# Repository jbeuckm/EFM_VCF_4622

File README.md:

# EFM_VCF_4622
Moog Taurus type Transistor Ladder LPF

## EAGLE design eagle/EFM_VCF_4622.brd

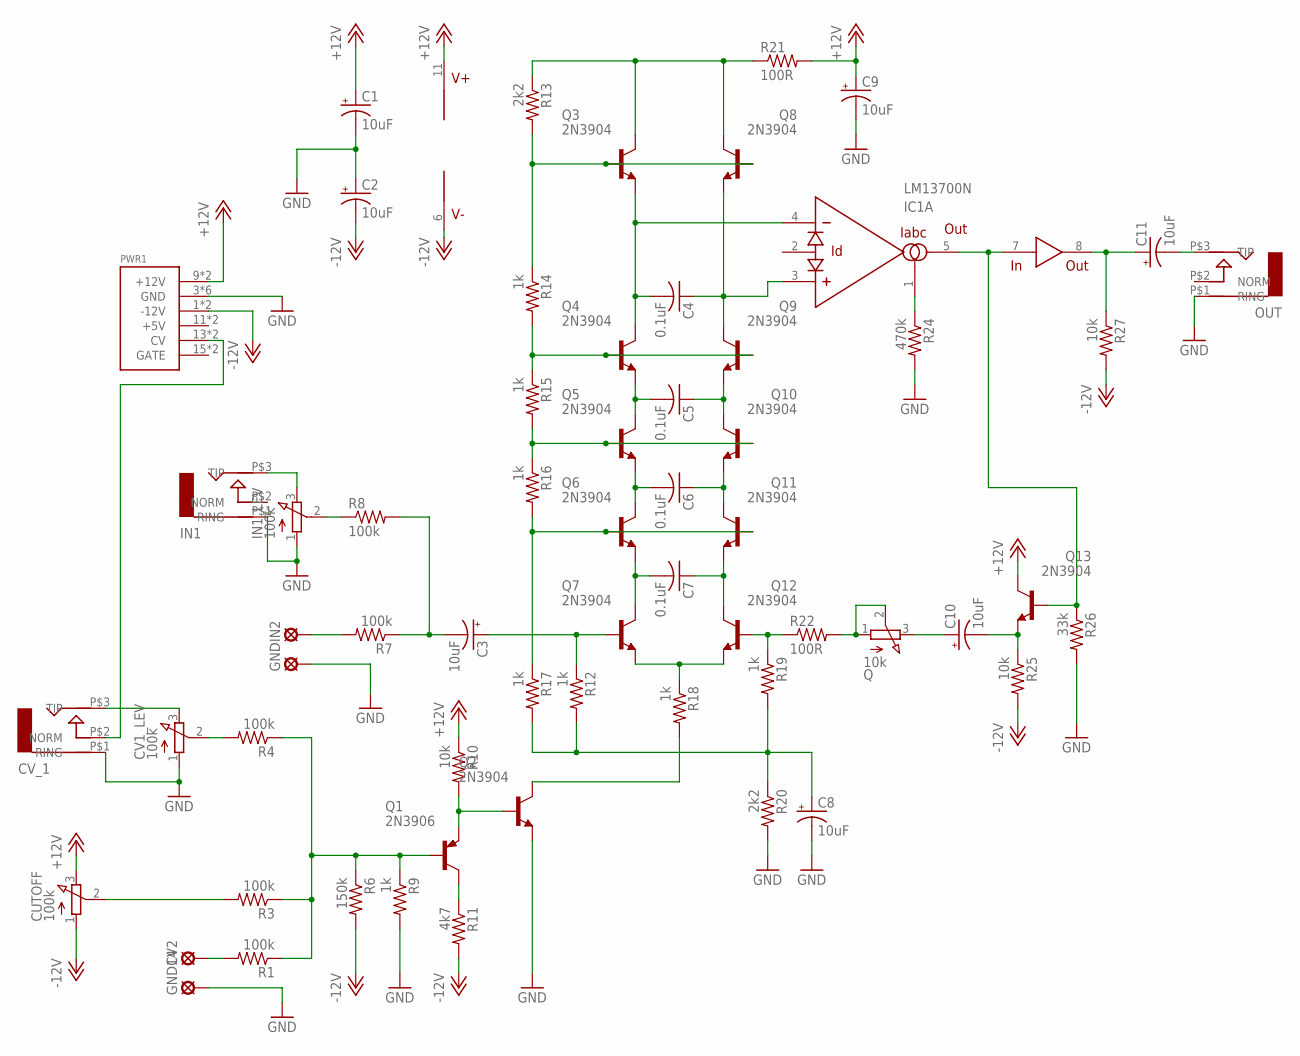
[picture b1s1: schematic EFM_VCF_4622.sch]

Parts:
C1, C2, C3, C8, C9: 10uF; B45181A
C4, C5, C6, C7: 0.1uF; C050-025X075
C10: 10uF; B45181C
C11: 10uF; B45181B
CUTOFF: 100k; 3RP/1610N
CV1_LEV: 100k; 3RP/1610N
CV2: LSP10
CV_1: AUDIO-JACK; ERTHENVAR-JACK-90DEG
GND, GND14: LSP10
IC1: LM13700N; DIL16
IN1: AUDIO-JACK; ERTHENVAR-JACK-90DEG
IN1_LEV: 100k; 3RP/1610N
IN2: LSP10
OUT: AUDIO-JACK; ERTHENVAR-JACK-90DEG
PWR1: POWER; POWER_16
Q: 10k; 3RP/1610N
Q1: 2N3906; TO92
Q2, Q3, Q4, Q5, Q6, Q7, Q8, Q9, Q10, Q11, Q12, Q13: 2N3904; TO92
R1, R3, R4, R7, R8: 100k; 0207/7
R6: 150k; 0207/7
R9, R12, R14, R15, R16, R17, R18, R19: 1k; 0207/7
R10: 10k; 0309/12
R11: 4k7; 0207/7
R13, R20: 2k2; 0207/7
R21, R22: 100R; 0207/7
R24: 470k; 0309/12
R25, R27: 10k; 0207/7
R26: 33k; 0207/7

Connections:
+12V: C1.+, C9.+, CUTOFF.3 (E), IC1.11 (V+), PWR1.9 (+12V), PWR1.10 (+12V), Q13.1 (C), R10.1, R21.2
-12V: C2.-, CUTOFF.1 (A), IC1.6 (V-), PWR1.1 (-12V), PWR1.2 (-12V), R6.2, R11.2, R25.2, R27.2
GND: C1.-, C2.+, C8.-, C9.-, CV1_LEV.1 (A), CV_1.P$1 (RING), GND.MP, GND14.MP, IN1.P$1 (RING), IN1_LEV.1 (A), OUT.P$1 (RING), PWR1.3 (GND), PWR1.4 (GND), PWR1.5 (GND), PWR1.6 (GND), PWR1.7 (GND), PWR1.8 (GND), Q2.3 (E), R9.2, R20.2, R24.2, R26.2
unnamed: IC1.1 (IABC), R24.1
unnamed: Q.1 (A), Q.2 (S), R22.2
unnamed: Q2.1 (C), R18.2
unnamed: Q7.3 (E), Q12.3 (E), R18.1
unnamed: IN2.MP, R7.2
unnamed: C3.-, R7.1, R8.2
unnamed: C3.+, Q7.2 (B), R12.1
unnamed: Q1.3 (E), Q2.2 (B), R10.2
unnamed: C4.2, IC1.4 (-IN), Q3.3 (E), Q4.1 (C)
unnamed: C10.+, Q.3 (E)
unnamed: CV2.MP, R1.2
unnamed: C4.1, IC1.3 (+IN), Q8.3 (E), Q9.1 (C)
unnamed: C6.1, Q10.3 (E), Q11.1 (C)
unnamed: C5.2, Q4.3 (E), Q5.1 (C)
unnamed: C5.1, Q9.3 (E), Q10.1 (C)
unnamed: C7.1, Q11.3 (E), Q12.1 (C)
unnamed: C7.2, Q6.3 (E), Q7.1 (C)
unnamed: IC1.5 (OUT), IC1.7 (IN), Q13.2 (B), R26.1
unnamed: Q1.2 (B), R1.1, R3.1, R4.1, R6.1, R9.1
unnamed: C8.+, R12.2, R17.2, R19.2, R20.1
unnamed: Q12.2 (B), R19.1, R22.1
unnamed: Q1.1 (C), R11.1
unnamed: C11.+, IC1.8 (OUT), R27.1
unnamed: C6.2, Q5.3 (E), Q6.1 (C)
unnamed: C11.-, OUT.P$3 (TIP)
unnamed: C10.-, Q13.3 (E), R25.1
unnamed: Q3.1 (C), Q8.1 (C), R13.1, R21.1
unnamed: Q3.2 (B), Q8.2 (B), R13.2, R14.1
unnamed: Q4.2 (B), Q9.2 (B), R14.2, R15.1
unnamed: Q5.2 (B), Q10.2 (B), R15.2, R16.1
unnamed: Q6.2 (B), Q11.2 (B), R16.2, R17.1
unnamed: CV1_LEV.2 (S), R4.2
unnamed: CV_1.P$2 (NORM), PWR1.13 (CV), PWR1.14 (CV)
unnamed: CUTOFF.2 (S), R3.2
unnamed: IN1_LEV.2 (S), R8.1
unnamed: IN1.P$3 (TIP), IN1_LEV.3 (E)
unnamed: CV1_LEV.3 (E), CV_1.P$3 (TIP)

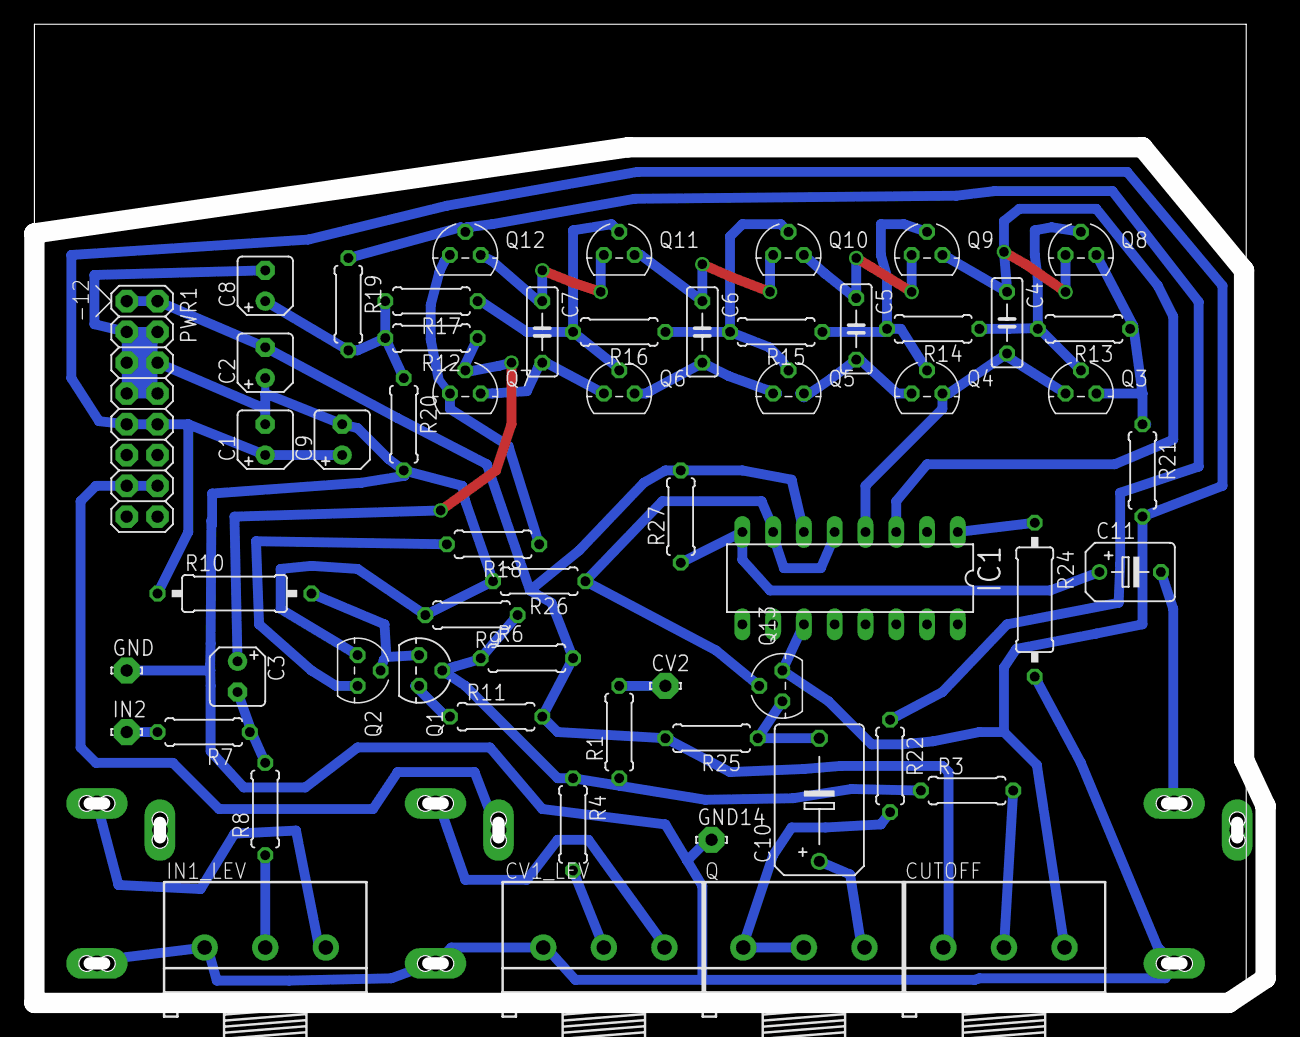
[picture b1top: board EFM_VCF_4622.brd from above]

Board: 2 copper layers, 101.6 x 79.9 mm, 61 parts (0 on the bottom side), 40 nets.

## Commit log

2015-12-03 board progress
2015-12-03 parts on the board
2015-12-03 trying routes
2015-12-04 routed
2015-12-04 fixed connections
2015-12-04 will try cut
2015-12-07 ready to cut
2015-12-09 first cut works but needs -12v cutoff mod
2015-12-09 it works
2015-12-09 neater layout and more cv and audio ins
2015-12-10 tidied still more
2015-12-10 new layout image
2016-01-05 board tweaks
2016-01-16 squared pcb with mounting holes
2016-07-19 updated panel gcode
